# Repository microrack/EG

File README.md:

# EG
Envelope generator (ADSR) for microrack

First prototype was maked in diptrace, now we migrate to KiCad, v.5 (you can find new version (in progress) in max_dev branch).

Repository contains only CAD sources, go to https://github.com/microrack/EG/releases page to get manufacturing files and printed version of CAD files.

This schematic has transient model in simulation directory. Schematic model opens in http://falstad.com/circuit/ online simulator. Open link and choose File > Open schematic file.

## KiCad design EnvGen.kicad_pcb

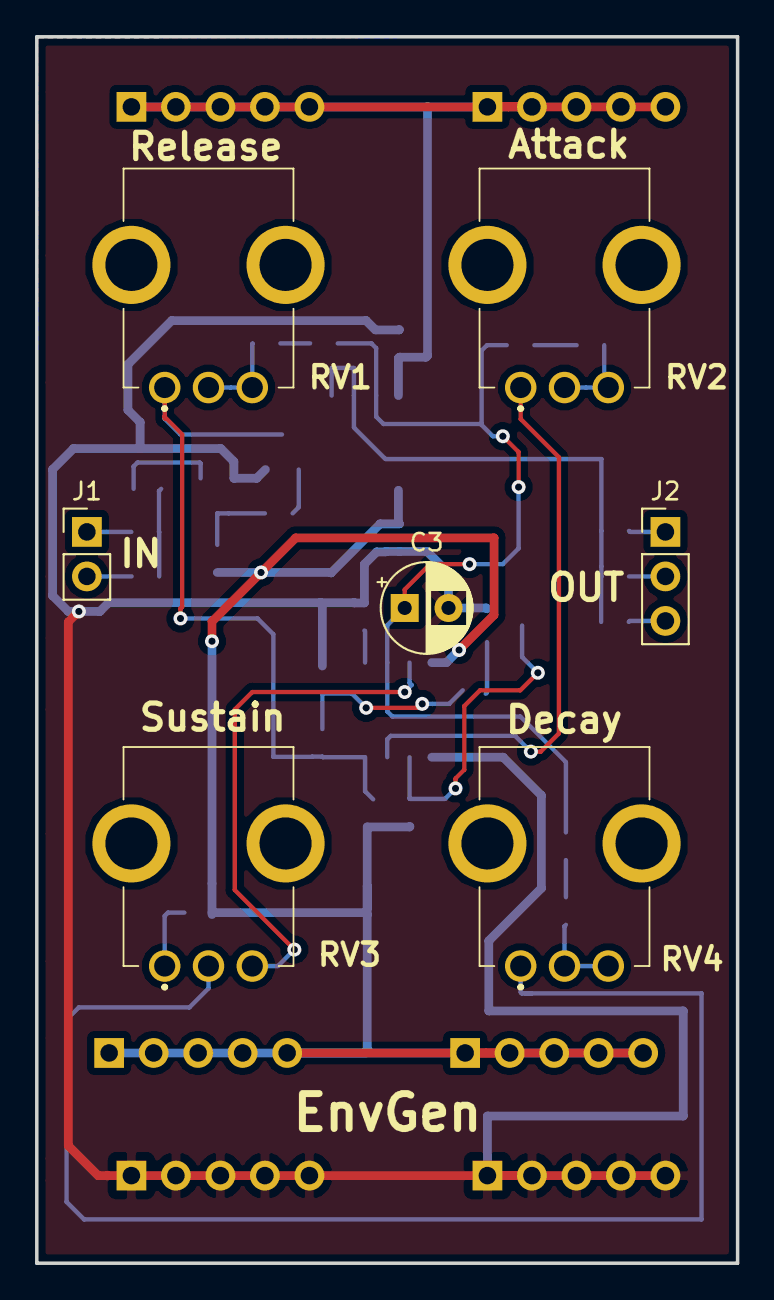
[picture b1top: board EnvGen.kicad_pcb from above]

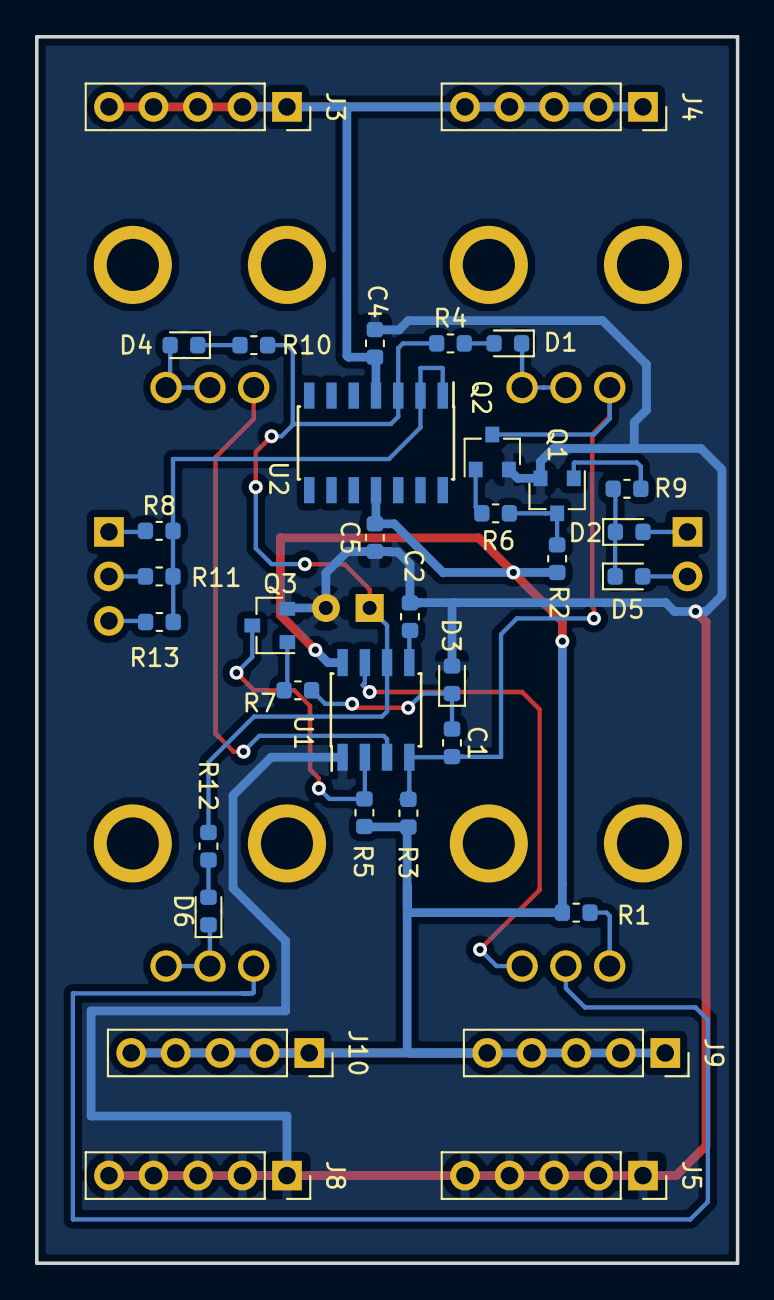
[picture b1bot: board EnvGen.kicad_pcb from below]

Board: 2 copper layers, 40.0 x 70.0 mm, 41 parts (34 on the bottom side), 29 nets.

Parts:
C1, C2: 10 nF; c0603
C3: 22x25v; cp_5x2_5
C4, C5: 0.1 uF; c0603
D1, D2, D3, D4, D5, D6: D; d0603
J1: Input; pls1x02
J2: Output; pls1x03
J3, J4, J5, J8, J9, J10: Conn_01x05_Male; pls1x05
Q1, Q2, Q3: BC817; SOT-23
R1, R2, R3, R5, R7, R9: 10K; r0603
R4, R8, R10, R11, R12, R13: 100R; r0603
R6: R; r0603
RV1, RV2, RV4: 100K; R0904N
RV3: 10K; R0904N
U1: NE555; soic-8
U2: LM324; soic-14

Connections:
+5V: C5.2, J9.1, J9.2, J9.3, J9.4, J9.5, J10.1, J10.2, J10.3, J10.4, J10.5, R1.2, R2.1, R3.1, R5.1, U1.8, U2.11
-5V: C4.1, J3.1, J3.2, J3.3, J3.4, J3.5, J4.1, J4.2, J4.3, J4.4, J4.5, U2.4
/OUT_2: J2.2, R11.2
GND: C2.2, C3.2, C4.2, C5.1, D3.2, J5.1, J5.2, J5.3, J5.4, J5.5, J8.1, J8.2, J8.3, J8.4, J8.5, Q1.2, Q2.2, Q3.2, U1.1
unnamed: C1.1, D3.1, R7.2
unnamed: C1.2, Q2.3, R3.2, RV1.1, U1.4
unnamed: C2.1, U1.5
unnamed: C3.1, R4.1, R10.1, R12.1, U1.6, U2.3
unnamed: D1.1, RV1.2, RV1.3
unnamed: D1.2, R4.2
unnamed: D2.1, D5.1, R9.2
unnamed: D2.2, J1.1
unnamed: D4.1, R10.2
unnamed: D4.2, RV2.2, RV2.3
unnamed: D5.2, J1.2
unnamed: D6.1, RV4.2, RV4.3
unnamed: D6.2, R12.2
unnamed: J2.1, R8.1
unnamed: J2.3, R13.1
unnamed: Q1.1, R9.1
unnamed: Q1.3, R2.2, R6.2
unnamed: Q2.1, R6.1
unnamed: Q3.1, R7.1
unnamed: Q3.3, R5.2, U1.2
unnamed: R1.1, RV3.1
unnamed: R8.2, R11.1, R13.2, U2.1, U2.2
unnamed: RV2.1, U1.3
unnamed: RV3.2, RV4.1
unnamed: RV3.3, U1.7

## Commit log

2019-03-15 add old prototype
2019-03-15 add kicad project (wip)
2019-03-31 copy from legacy repo
2019-04-05 Изменена плата до размера 40х70 мм
2019-04-05 Изменены абсолютные пути к библиотекам и моделям на отнасительные. В схемах резисторы европейского УГО заменены на Российские
2019-04-10 Косметические изменения в схемах Плата 40х70 мм. Добавленны подписи компонентов и регуляторов на плате
